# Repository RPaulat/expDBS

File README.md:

# expDBS – Experimental Deep Brain Stimulation Data and Materials (under construction)

Repository accompanying the manuscript:

> *“Wireless lightweight implantable pulse generators enable chronic dual‑target deep brain stimulation in rodent disease models”*

This repository contains selected data, code, and additional supplementary materials related to the experiments and analyses presented in the manuscript. More data and material may be provided upon reasonable request.

---

## Repository folder structure (last updated 04/21/2026)

The current structure of this repository is as follows:

- **`expDBS/`**
  - **`CodeWarrior_µC_IPGsoftware/`**  
    - Souce Code (Code Warrior) used for processing stimulation parameters throughout C & Assembler software.
  - **`Documents/`**  
    - Additional documentation, extended FEM simulations.  
  - **`Electrode/`**  
    - Renderings, plots and pictures.
  - **`LTspice_circuit_simulations/`**
    - Simulation files, supplementary and additional material.
  - **`Schematic&Layout/`**  
    - Schematics, layouted board files (EAGLE, FUSION), or firmware sources for the wireless lightweight implantable pulse generators.   
  - **`Statistics&Pictures/`**
    - Data Analysis behavioral data, R-Studio plots or neurophysiological recordings.
  - - **`Videos/`**
    - example video referenced in the manuscript or additional material.  
  - **`README.md`**  
    - This file, describing the repository contents and usage.  
  - **`LICENSE`**  
    - License file for the code and associated materials.

---

## Data availability policy

A selection of data, videos, or other additional material is available in this repository:  
https://github.com/RPaulat/expDBS

Further data and material may be made available upon reasonable request. Users are welcome to contact the corresponding authors via email.

---

## License and usage

Unless otherwise stated, the code is open source.  
Data are shared for non‑commercial research purposes in accordance with institutional data‑use and animal‑ethics policies.

---

## Authors and contact

- **Corresponding authors**
- **Raik Paulat** – *First corresponding author*  
  
- **Leif Koschützke** – *Second corresponding author*  

---

## How to cite

If you use data or code from this repository, please cite the associated publication:

> *Wireless lightweight implantable pulse generators enable chronic dual‑target deep brain stimulation in rodent disease models*  
> [full citation after publication, e.g. Sci. Rep. YYYY; DOI: ... will follow.]

---

## Acknowledgements

We thank our institutions and funding agencies for support. Facilities and expertise from Core Facility Workshop (CWW) are also gratefully acknowledged.

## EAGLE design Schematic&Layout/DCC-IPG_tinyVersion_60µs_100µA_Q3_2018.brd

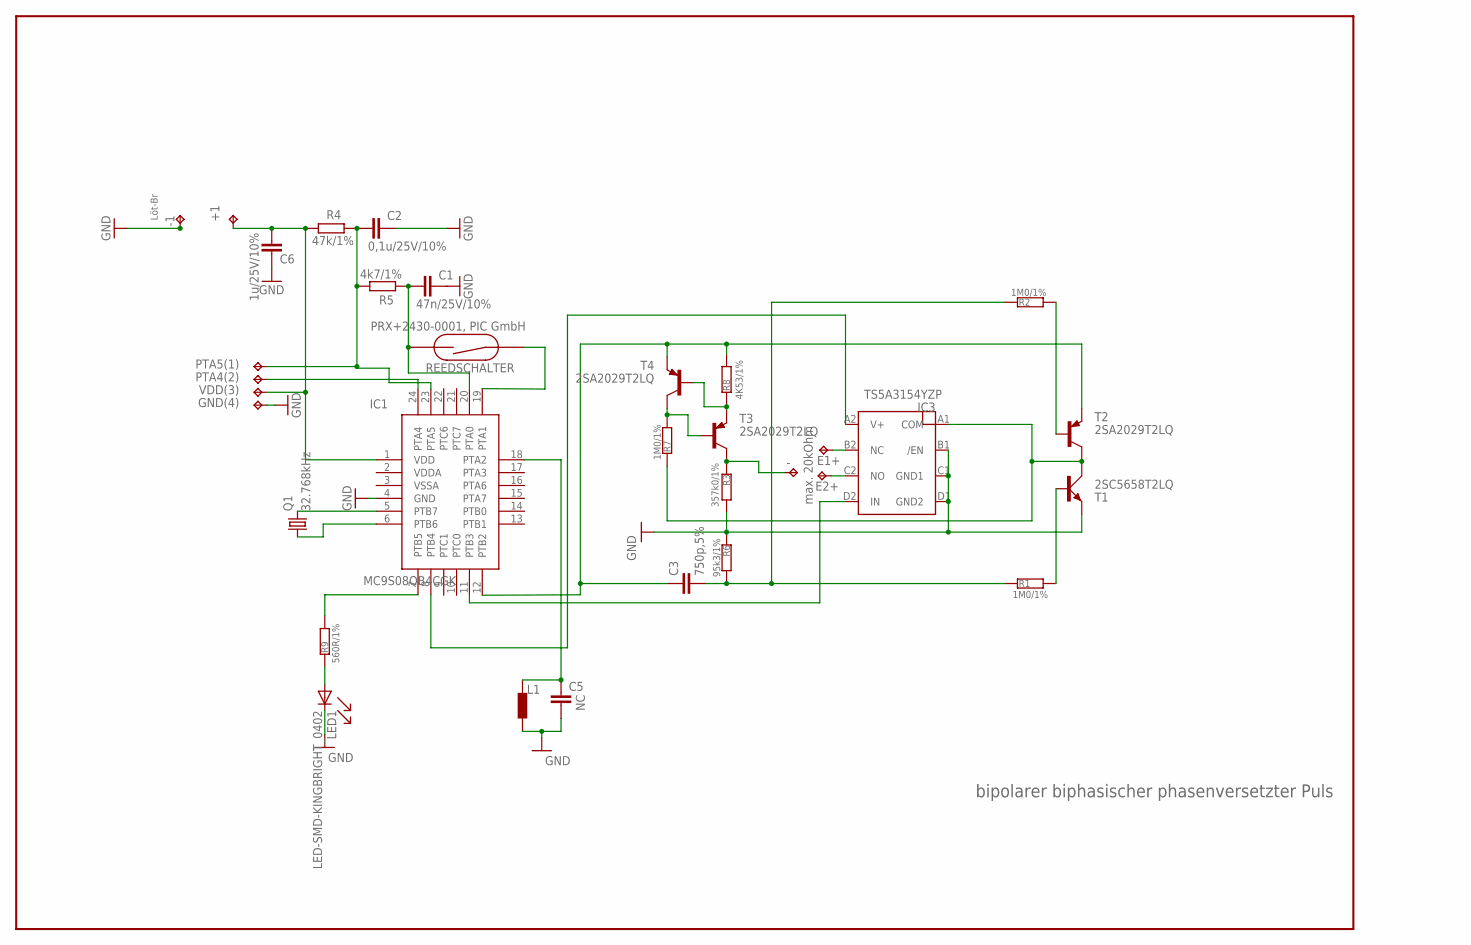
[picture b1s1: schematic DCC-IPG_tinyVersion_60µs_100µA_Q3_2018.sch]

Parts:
+1: TPTP11SQ; TP11SQ
-: TPTP07SQ; TP07SQ
-1: TPTP11SQ; TP11SQ
C1: 47n/25V/10%; C0201
C2: 0,1u/25V/10%; C0201
C3: 750p,5%; C0201
C5: NC; C1608
C6: 1u/25V/10%; C0201
E1+, E2+: TPTP07SQ; TP07SQ
GND(4): TPTP04SQ; TP04SQ
IC1: MC9S08QB4CGK; QFN_24
IC3: TS5A3154YZP; WCSP
LED1: LED-SMD-KINGBRIGHT_0402; LED_0403
PTA4(2), PTA5(1): TPTP04SQ; TP04SQ
Q1: 32.768kHz; SMT
R1, R2, R7: 1M0/1%; R0201
R3: 357k0/1%; R0201
R4: 47k/1%; R0201
R5: 4k7/1%; R0201
R6: 95k3/1%; R0201
R8: 4K53/1%; R0201
R9: 560R/1%; R0201
REEDSCHALTER: PRX+2430-0001, PIC GmbH; PRX+2452
T1: 2SC5658T2LQ; VMT3
T2, T3, T4: 2SA2029T2LQ; VMT3
VDD(3): TPTP04SQ; TP04SQ

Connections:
3V_SOURCE_ON_OFF: C3.1, IC1.12 (PTB2), R8.1, T2.E, T4.E
ANALOG_SWITCH: IC1.8 (PTB4), IC3.A2 (V+)
ANALOG_SWITCH_DIRECTION: IC1.11 (PTB3), IC3.D2 (IN)
CURRENT_IN: IC3.A1 (COM), R7.2, T1.C, T2.C
CURRENT_SWITCHES: C3.2, R1.2, R2.2, R6.2
ELECTRODE_1+: E1+.TP, IC3.B2 (NC)
ELECTRODE_2+: E2+.TP, IC3.C2 (NO)
GND: -1.TP, C1.1, C2.1, C5.2, C6.1, GND(4).P$1, IC1.4 (GND), IC3.B1 (/EN), IC3.C1 (GND1), IC3.D1 (GND2), LED1.C, R3.2, R6.1, T1.E
unnamed: R1.1, T1.B
unnamed: R2.1, T2.B
unnamed: IC1.7 (PTB5), R9.1
unnamed: IC1.19 (PTA1), REEDSCHALTER.P$1
unnamed: R8.2, T3.E, T4.B
unnamed: C5.1, IC1.18 (PTA2)
unnamed: IC1.5 (PTB7), Q1.P$2 (2)
unnamed: LED1.A, R9.2
unnamed: IC1.6 (PTB6), Q1.P$1 (1)
unnamed: IC1.24 (PTA4), PTA4(2).P$1
unnamed: R7.1, T3.B, T4.C
REF.-OUT: -.TP, R3.1, T3.C
S$9: C1.2, IC1.20 (PTA0), R5.1, REEDSCHALTER.P$2
S$12: C2.2, IC1.23 (PTA5), PTA5(1).P$1, R4.2, R5.2
VDD: +1.TP, C6.2, IC1.1 (VDD), R4.1, VDD(3).P$1

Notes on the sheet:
bipolarer biphasischer phasenversetzter Puls
Löt-Br
max. 20kOhm

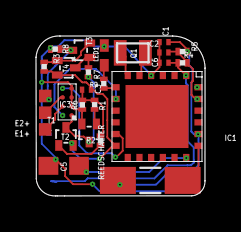
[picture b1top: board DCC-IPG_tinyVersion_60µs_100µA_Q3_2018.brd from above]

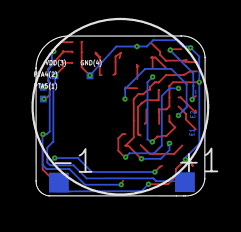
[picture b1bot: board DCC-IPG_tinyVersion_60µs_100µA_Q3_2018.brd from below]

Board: 8 copper layers, 9.4 x 8.9 mm, 32 parts (6 on the bottom side), 23 nets.

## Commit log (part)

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2024-01-22 Testpicture from old folder
2024-01-23 schematic test file
2026-04-21 Clarify description of repository contents
    Updated wording for clarity in the README.
2026-04-21 Update repository folder structure last updated date
